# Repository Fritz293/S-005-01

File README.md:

# Raspberry Pi Multi-Status LED HAT

An industrial-grade Raspberry Pi HAT designed for high-visibility status monitoring using the **OSRAM DISPLIX® P3333 RGB LED** array. This board features professional-level power protection and follows the official Raspberry Pi HAT specifications.

## 🚀 Current Progress: Phase 1 (Schematic Complete)
- [x] Power Filtering & ESD Protection
- [x] High-Efficiency Reverse Polarity Protection (P-MOSFET)
- [x] Logic Level Shifting for 5V LED Driving
- [x] HAT ID EEPROM Implementation
- [ ] PCB Layout & Routing (Next Step)

---

## 🛠 Hardware Specifications

### 1. Power & Protection
To ensure the Raspberry Pi 5 remains stable during transient spikes, the 5V rail includes:
* **Reverse Polarity Protection:** Implemented via an **AO3401A P-Channel MOSFET**. This provides protection with negligible voltage drop (<0.05V) compared to a standard Schottky diode.
* **Overvoltage Protection:** Dual **5.6V 3W Zener/TVS diodes** ($D10, D11$).
* **Current Limiting:** A **375mA Fuse (F1)** protects the logic from downstream shorts.
* **Filtering:** 10µF and 100nF ceramic/tantalum capacitors for noise decoupling.

### 2. LED Driver Circuit
The board drives an **OSRAM KRTB LSLPS1.32** RGB LED via a high-side/low-side configuration:
* **Switching:** Three **BSS138 N-MOSFETs** act as logic-level shifters, allowing the Pi's 3.3V GPIOs to safely switch the 5V LED rail.
* **Current Calibration (at 20mA):**
    * **Red:** 150Ω
    * **Green:** 120Ω (Updated for Osram Vf)
    * **Blue:** 110Ω (Updated for Osram Vf)
* **ESD Safety:** **PESD5V0S1UL** protection diodes are placed at the external connector and MOSFET drains to prevent static damage.

### 3. Controller Interface
| Function | GPIO | Physical Pin |
| :--- | :--- | :--- |
| **Power/Idle** | GPIO 17 | Pin 11 |
| **Media Activity** | GPIO 27 | Pin 13 |
| **Error State** | GPIO 22 | Pin 15 |
| **ID_SDA** | EEPROM Data | Pin 27 |
| **ID_SCL** | EEPROM Clock | Pin 28 |

---

## 📝 Design Notes
> **Note on EEPROM Wiring:** The AT24C32 EEPROM is connected to the dedicated `ID_SD` and `ID_SC` pins (Pins 27/28) to allow the Raspberry Pi to automatically load the device tree overlay at boot.

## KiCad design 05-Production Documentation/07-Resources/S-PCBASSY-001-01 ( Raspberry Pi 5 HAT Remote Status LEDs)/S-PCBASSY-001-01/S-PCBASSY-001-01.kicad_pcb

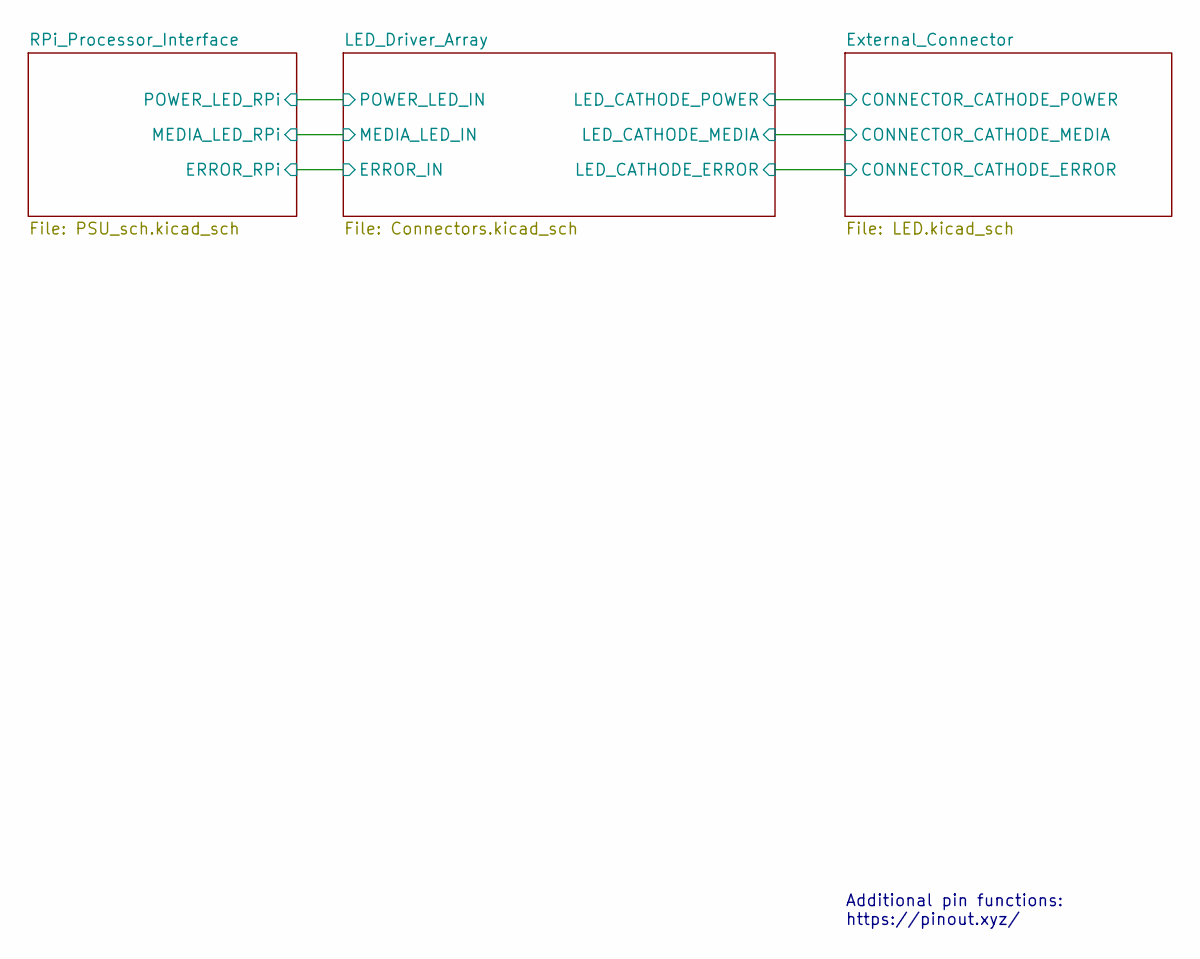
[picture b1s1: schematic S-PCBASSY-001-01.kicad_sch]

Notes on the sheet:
Additional pin functions: https://pinout.xyz/

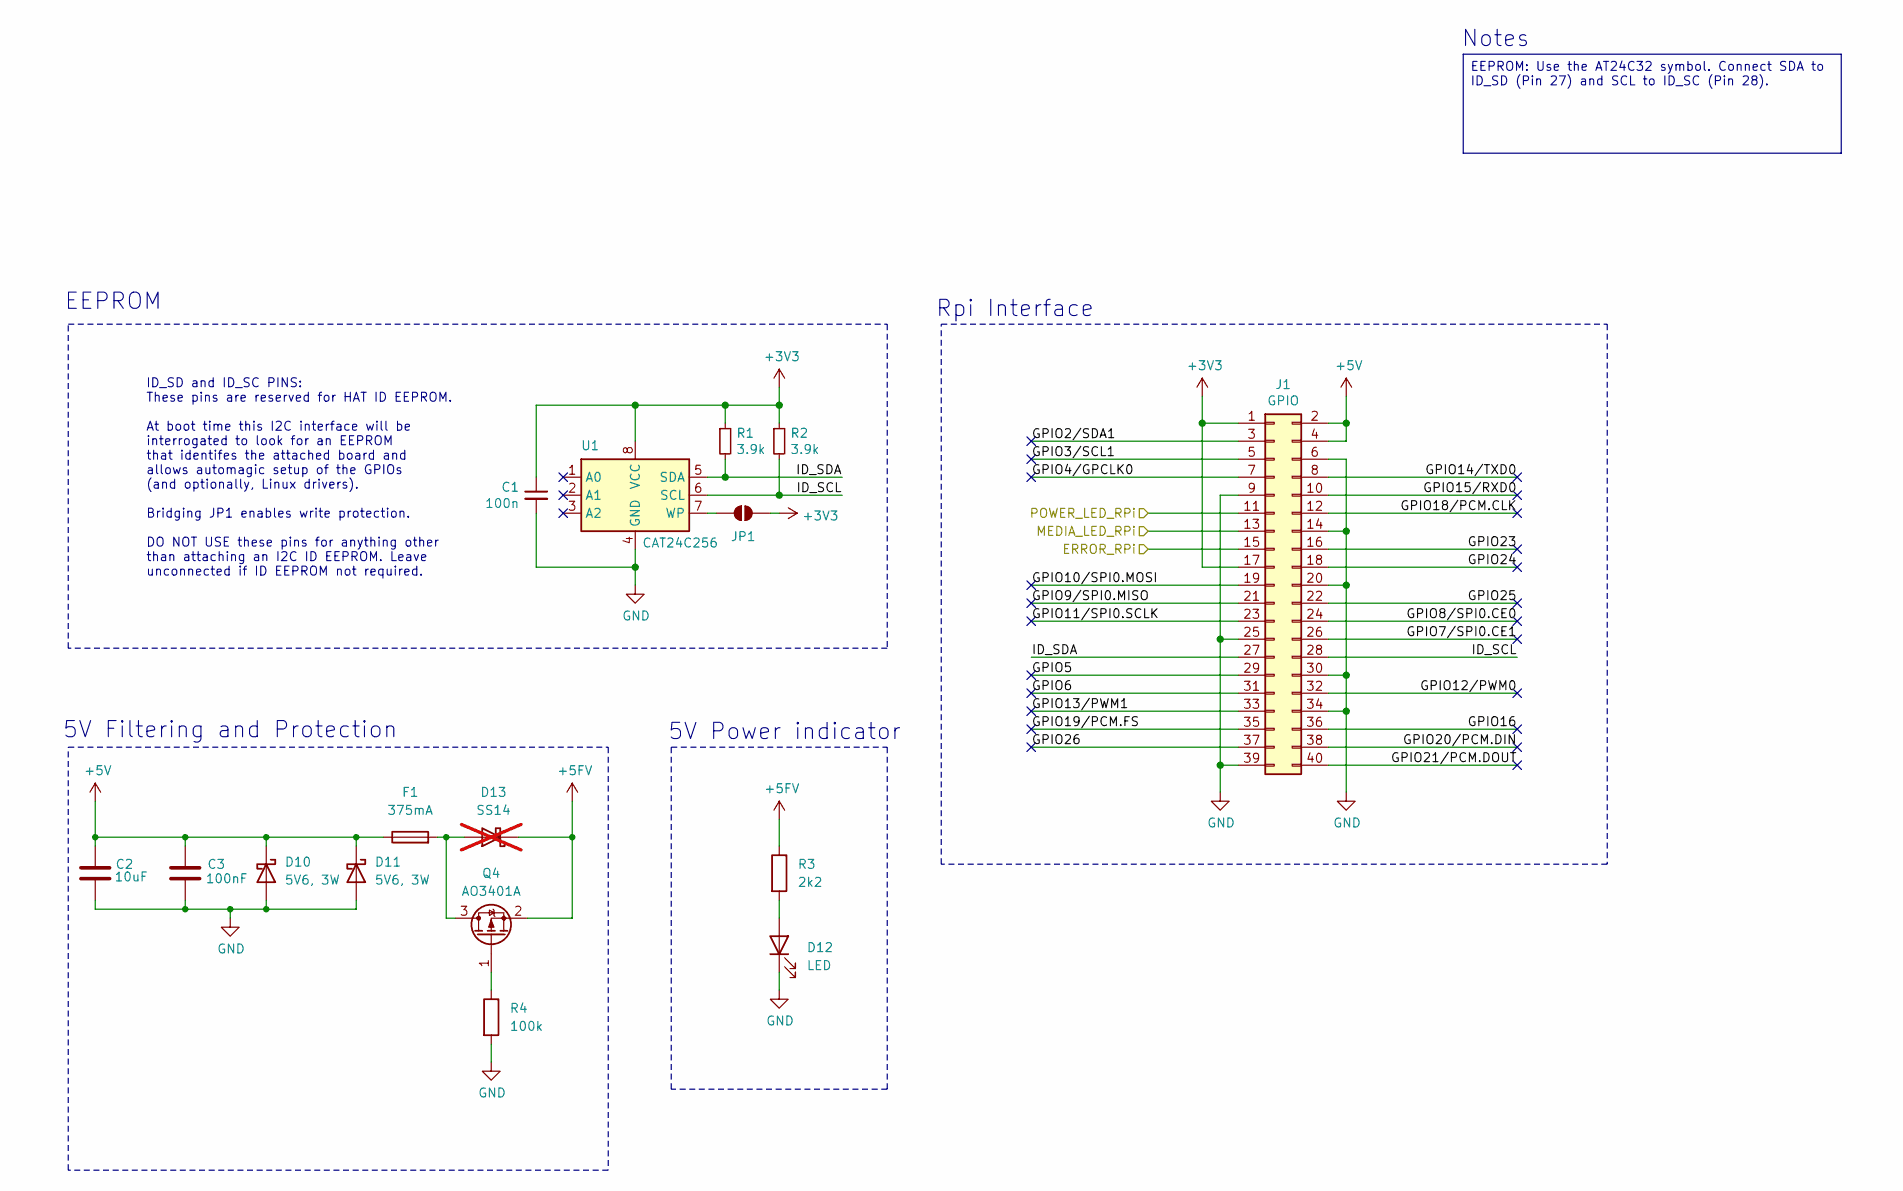
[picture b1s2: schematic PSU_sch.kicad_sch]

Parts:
C1: 100n; C_0603_1608Metric
C2: KEMET T491A106K016AT; CP_EIA-3216-18_Kemet-A
C3: Samsung CL21B104KBCNNNC; C_0805_2012Metric
D10, D11: 5V6, 3W; D_SMA
D12: LED; LED_0603_1608Metric
D13: SS14; D_SMA; not fitted
F1: 375mA; Fuse_0603_1608Metric
J1: GPIO; PinSocket_2x20_P2.54mm_Vertical
JP1: ID_WP; PinHeader_1x02_P2.54mm_Vertical_SMD_Pin1Left
Q4: AO3401A; SOT-23
R1, R2: 3.9k; C_0603_1608Metric
R3: 2k2; R_0603_1608Metric_Pad0.98x0.95mm_HandSolder
R4: 100k; R_0603_1608Metric_Pad0.98x0.95mm_HandSolder
U1: CAT24C256; SOIC-8_3.9x4.9mm_P1.27mm

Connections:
+3V3: C1.1, J1.1, J1.17, JP1.2 (B), R1.1, R2.1, U1.8 (VCC)
+5FV: D13.1 (K), Q4.2 (S), R3.1; also elsewhere on the board
+5V: C2.1, C3.1, D10.1 (K), D11.1 (K), F1.1, J1.2, J1.4
/LED_Driver_Array/ERROR_IN: J1.15; also elsewhere on the board
/LED_Driver_Array/MEDIA_LED_IN: J1.13; also elsewhere on the board
/LED_Driver_Array/POWER_LED_IN: J1.11; also elsewhere on the board
/RPi_Processor_Interface/GPIO2/SDA1: J1.3
/RPi_Processor_Interface/GPIO3/SCL1: J1.5
/RPi_Processor_Interface/GPIO4/GPCLK0: J1.7
/RPi_Processor_Interface/GPIO5: J1.29
/RPi_Processor_Interface/GPIO6: J1.31
/RPi_Processor_Interface/GPIO7/SPI0.CE1: J1.26
/RPi_Processor_Interface/GPIO8/SPI0.CE0: J1.24
/RPi_Processor_Interface/GPIO9/SPI0.MISO: J1.21
/RPi_Processor_Interface/GPIO10/SPI0.MOSI: J1.19
/RPi_Processor_Interface/GPIO11/SPI0.SCLK: J1.23
/RPi_Processor_Interface/GPIO12/PWM0: J1.32
/RPi_Processor_Interface/GPIO13/PWM1: J1.33
/RPi_Processor_Interface/GPIO14/TXD0: J1.8
/RPi_Processor_Interface/GPIO15/RXD0: J1.10
/RPi_Processor_Interface/GPIO16: J1.36
/RPi_Processor_Interface/GPIO18/PCM.CLK: J1.12
/RPi_Processor_Interface/GPIO19/PCM.FS: J1.35
/RPi_Processor_Interface/GPIO20/PCM.DIN: J1.38
/RPi_Processor_Interface/GPIO21/PCM.DOUT: J1.40
/RPi_Processor_Interface/GPIO23: J1.16
/RPi_Processor_Interface/GPIO24: J1.18
/RPi_Processor_Interface/GPIO25: J1.22
/RPi_Processor_Interface/GPIO26: J1.37
/RPi_Processor_Interface/ID_SCL: J1.28, R2.2, U1.6 (SCL)
/RPi_Processor_Interface/ID_SDA: J1.27, R1.2, U1.5 (SDA)
GND: C1.2, C2.2, C3.2, D10.2 (A), D11.2 (A), D12.1 (K), J1.6, J1.9, J1.14, J1.20, J1.25, J1.30, J1.34, J1.39, R4.2, U1.4 (GND); also elsewhere on the board
unnamed: D12.2 (A), R3.2
unnamed: D13.2 (A), F1.2, Q4.3 (D)
unnamed: JP1.1 (A), U1.7 (WP)
unnamed: Q4.1 (G), R4.1

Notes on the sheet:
5V Filtering and Protection
5V Power indicator
EEPROM
Rpi Interface
ID_SD and ID_SC PINS: These pins are reserved for HAT ID EEPROM. At boot time this I2C interface will be interrogated to look for an EEPROM that identifes the attached board and allows automagic setup of the GPIOs (and optionally, Linux drivers). Bridging JP1 enables write protection. DO NOT USE th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
Notes
EEPROM: Use the AT24C32 symbol. Connect SDA to ID_SD (Pin 27) and SCL to ID_SC (Pin 28).

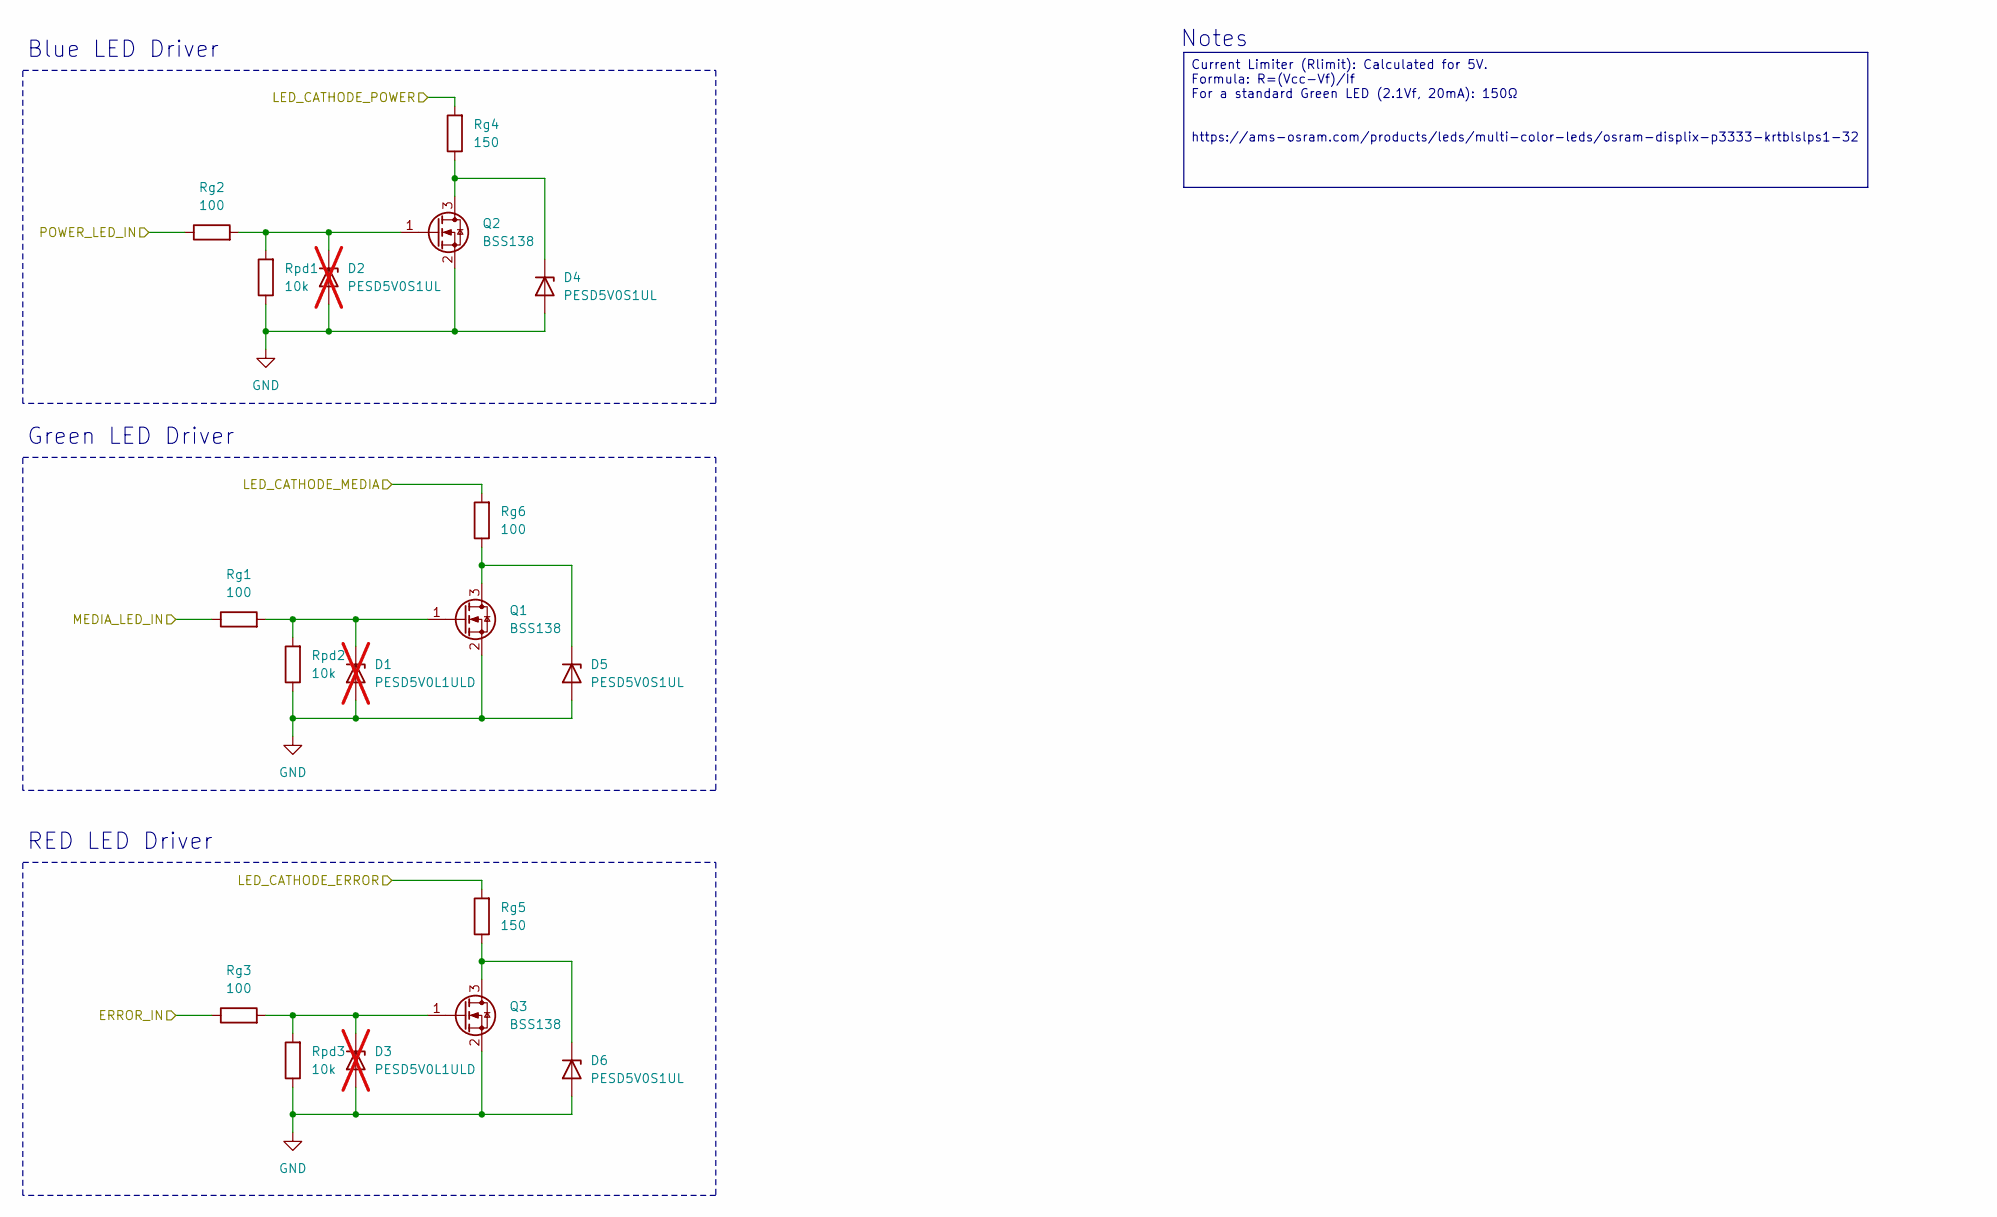
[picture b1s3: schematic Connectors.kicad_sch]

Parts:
D1, D3: PESD5V0L1ULD; D_SOD-882D; not fitted
D2: PESD5V0S1UL; D_SOD-882; not fitted
D4, D5, D6: PESD5V0S1UL; D_SOD-882
Q1, Q2, Q3: BSS138; SOT-23
Rg1, Rg2, Rg6: 100; C_0603_1608Metric
Rg3: 100; R_0603_1608Metric_Pad0.98x0.95mm_HandSolder
Rg4, Rg5: 150; C_0603_1608Metric
Rpd1, Rpd2, Rpd3: 10k; C_0603_1608Metric

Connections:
/External_Connector/CONNECTOR_CATHODE_ERROR: Rg5.2; also elsewhere on the board
/External_Connector/CONNECTOR_CATHODE_MEDIA: Rg6.2; also elsewhere on the board
/External_Connector/CONNECTOR_CATHODE_POWER: Rg4.2; also elsewhere on the board
/LED_Driver_Array/ERROR_IN: Rg3.1; also elsewhere on the board
/LED_Driver_Array/MEDIA_LED_IN: Rg1.1; also elsewhere on the board
/LED_Driver_Array/POWER_LED_IN: Rg2.1; also elsewhere on the board
GND: D1.2 (A), D2.2 (A), D3.2 (A), D4.2 (A), D5.2 (A), D6.2 (A), Q1.2 (S), Q2.2 (S), Q3.2 (S), Rpd1.1, Rpd2.1, Rpd3.1; also elsewhere on the board
unnamed: D1.1 (K), Q1.1 (G), Rg1.2, Rpd2.2
unnamed: D2.1 (K), Q2.1 (G), Rg2.2, Rpd1.2
unnamed: D3.1 (K), Q3.1 (G), Rg3.2, Rpd3.2
unnamed: D4.1 (K), Q2.3 (D), Rg4.1
unnamed: D5.1 (K), Q1.3 (D), Rg6.1
unnamed: D6.1 (K), Q3.3 (D), Rg5.1

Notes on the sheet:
Notes
RED LED Driver
Green LED Driver
Blue LED Driver
Current Limiter (Rlimit​): Calculated for 5V. Formula: R=(Vcc​−Vf​)/If​ For a standard Green LED (2.1Vf​, 20mA): 150Ω https://ams-osram.com/products/leds/multi-color-leds/osram-displix-p3333-krtblslps1-32

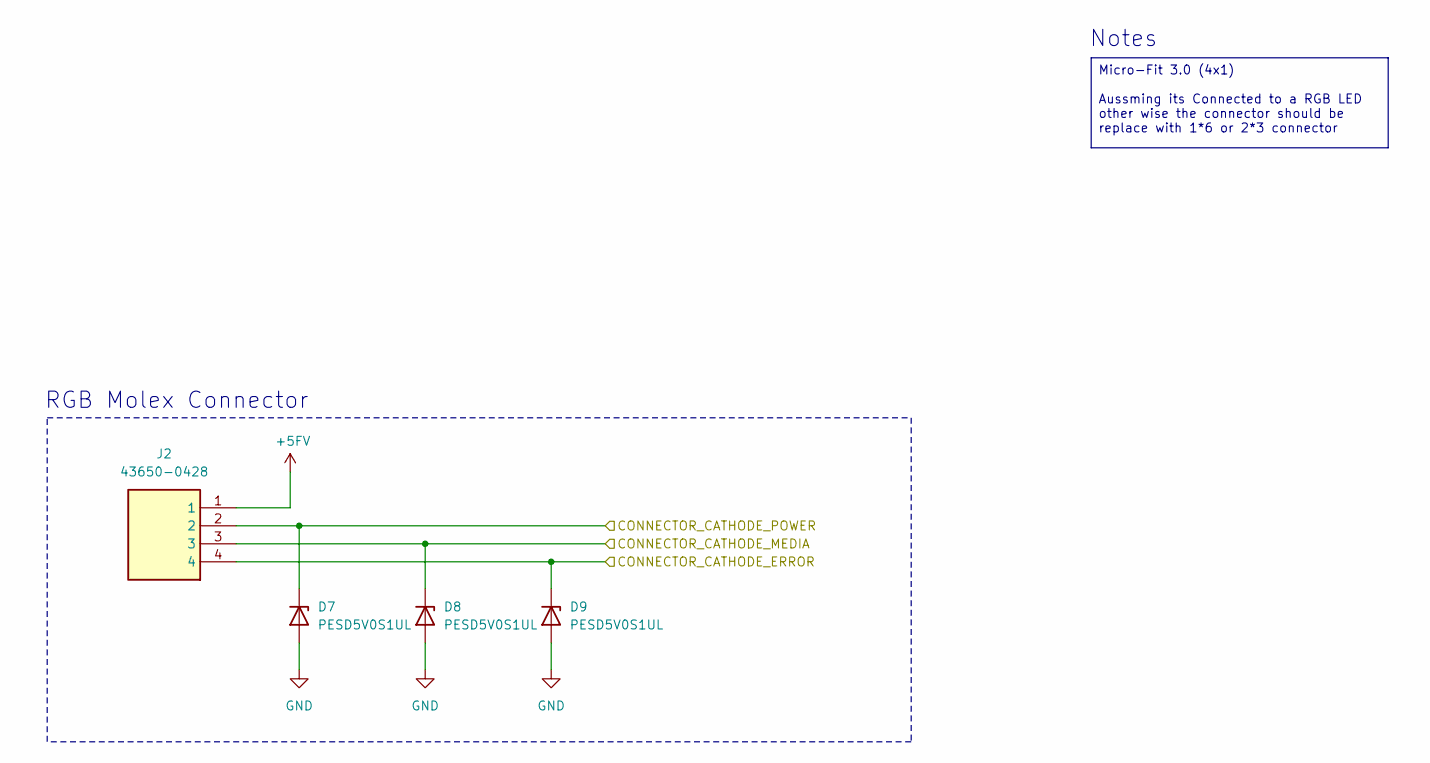
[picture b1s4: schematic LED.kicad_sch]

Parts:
D7, D8, D9: PESD5V0S1UL; D_SOD-882
J2: 43650-0428; 43650-04YY_272829; Manufacturer_Part_Number 43650-0428; Mouser Part Number 538-43650-0428

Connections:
+5FV: J2.1; also elsewhere on the board
/External_Connector/CONNECTOR_CATHODE_ERROR: D9.1 (K), J2.4; also elsewhere on the board
/External_Connector/CONNECTOR_CATHODE_MEDIA: D8.1 (K), J2.3; also elsewhere on the board
/External_Connector/CONNECTOR_CATHODE_POWER: D7.1 (K), J2.2; also elsewhere on the board
GND: D7.2 (A), D8.2 (A), D9.2 (A); also elsewhere on the board

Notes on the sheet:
Notes
RGB Molex Connector
Micro-Fit 3.0 (4x1) Aussming its Connected to a RGB LED other wise the connector should be replace with 1*6 or 2*3 connector

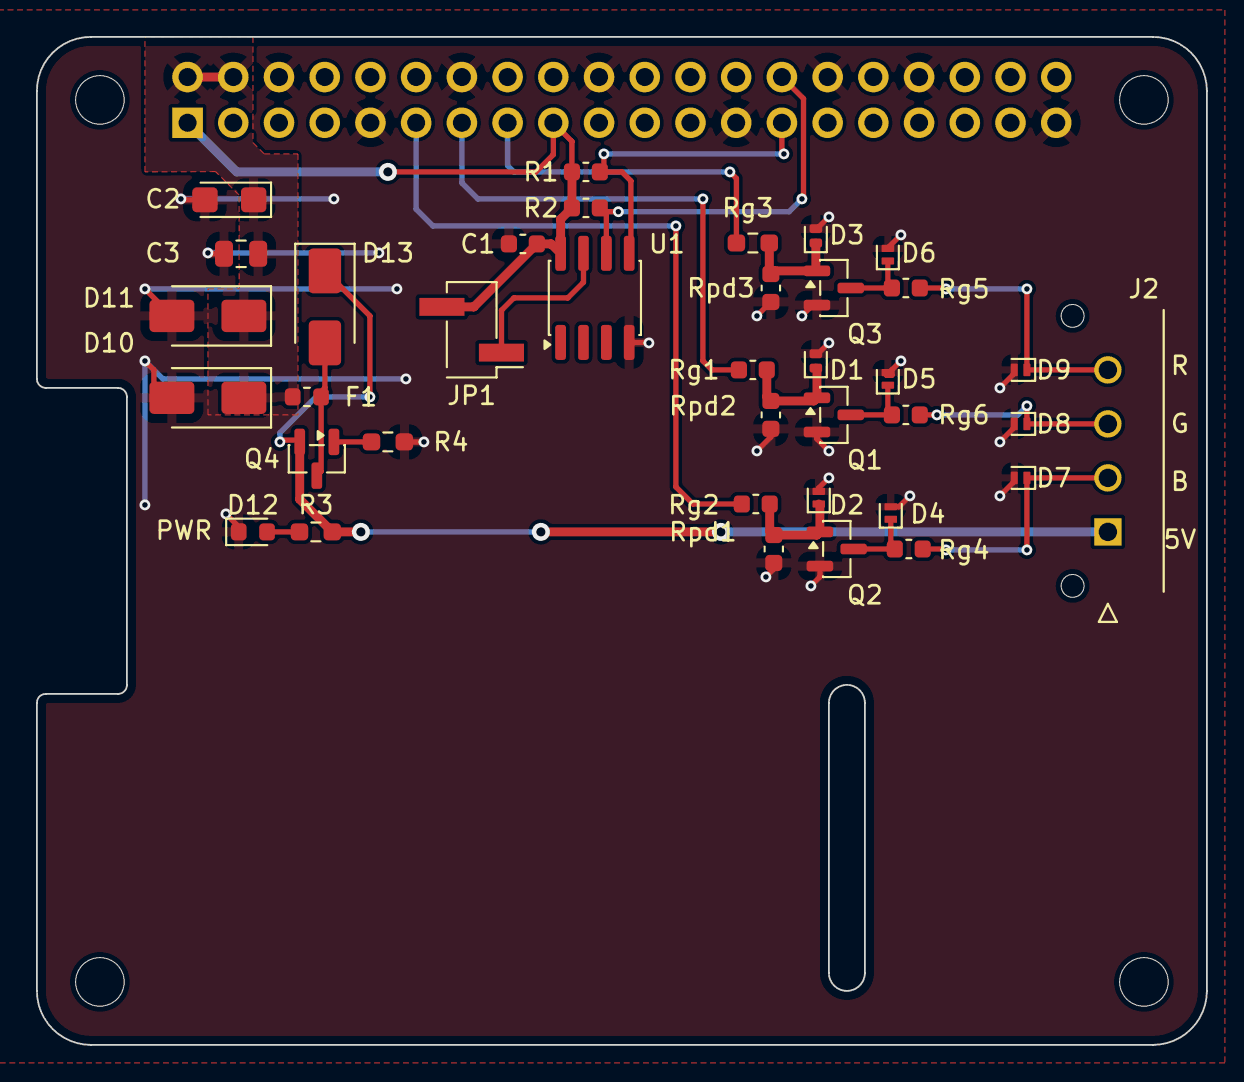
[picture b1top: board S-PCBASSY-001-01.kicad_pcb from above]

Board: 2 copper layers, 65.0 x 56.0 mm, 42 parts (1 on the bottom side), 22 nets.

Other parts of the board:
MH1, MH2, MH3, MH4: MountingHole_2.7mm_M2.5

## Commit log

2026-02-25 Init Folder Structure
2026-02-25 Board Outline done
2026-02-25 Updated Board Outline
2026-02-25 Added LED Mosfet Drivers
2026-02-25 WIP - LED Driver and Started with Connectors
2026-02-28 Connector added with TVS still need to add polarity Protection
2026-02-28 Added Decolping caps
2026-02-28 Rpi Filetring and protection added
2026-02-28 Schematics done
2026-02-28 Updated Readme For progress tracking
2026-02-28 ERC Completed and passed
2026-02-28 Saved
2026-02-28 Imported Components to PCB
2026-02-28 Done for now will ocntinue later
2026-02-28 Layout done
2026-02-28 PCB Routing done
2026-02-28 Errors Resolved Ready for Docs
2026-02-28 Done
2026-02-28 Forgot the Gerbers
